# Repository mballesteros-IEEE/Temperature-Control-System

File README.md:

Temperature-Control-System
========================================

Automatic system to control temperature in a house. Project in development

Authors Manuel Ballesteros and Damián Junquera

Repository Contents
-------------------

* **/Firmware** - Example code 
* **/Hardware** - Eagle design files (.brd, .sch)
* **/Libraries** - Libraries for use with
* **/Software** - Related software
* **/Documentation** - Data sheets, additional product information

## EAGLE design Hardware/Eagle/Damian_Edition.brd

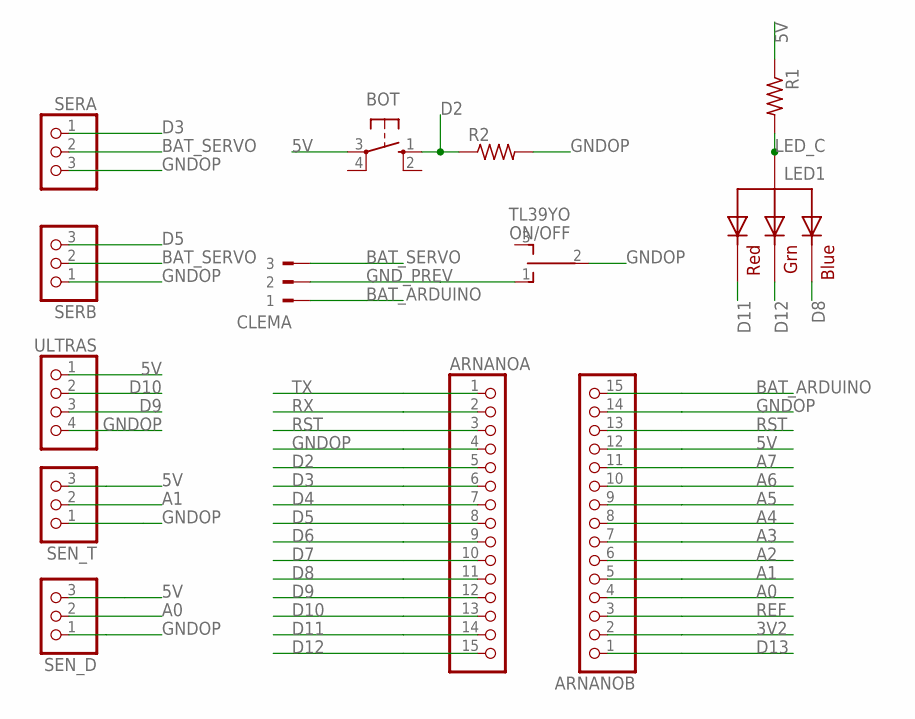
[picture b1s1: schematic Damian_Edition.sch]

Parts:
ARNANOA: PINHD-1X15; 1X15
ARNANOB: PINHD-1X15; 1X15
BOT: 10-XX; B3F-10XX
CLEMA: 90-3
LED1: RGBLED_CA-5MM; LED5MMRGB
ON/OFF: TL39YO; TL3XYO
R1, R2: R-US_0207/2V; 0207/2V
SEN_D: PINHD-1X3; 1X03
SEN_T: PINHD-1X3; 1X03
SERA: PINHD-1X3; 1X03
SERB: PINHD-1X3; 1X03
ULTRAS: PINHD-1X4; 1X04

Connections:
3V2: ARNANOB.2
5V: ARNANOB.12, BOT.3, R1.1, SEN_D.3, SEN_T.3, ULTRAS.1
A0: ARNANOB.4, SEN_D.2
A1: ARNANOB.5, SEN_T.2
A2: ARNANOB.6
A3: ARNANOB.7
A4: ARNANOB.8
A5: ARNANOB.9
A6: ARNANOB.10
A7: ARNANOB.11
BAT_ARDUINO: ARNANOB.15, CLEMA.1
BAT_SERVO: CLEMA.3, SERA.2, SERB.2
D2: ARNANOA.5, BOT.1 (S), R2.1
D3: ARNANOA.6, SERA.1
D4: ARNANOA.7
D5: ARNANOA.8, SERB.3
D6: ARNANOA.9
D7: ARNANOA.10
D8: ARNANOA.11, LED1.4 (BLUE)
D9: ARNANOA.12, ULTRAS.3
D10: ARNANOA.13, ULTRAS.2
D11: ARNANOA.14, LED1.1 (RED)
D12: ARNANOA.15, LED1.3 (GREEN)
D13: ARNANOB.1
GNDOP: ARNANOA.4, ARNANOB.14, ON/OFF.2, R2.2, SEN_D.1, SEN_T.1, SERA.3, SERB.1, ULTRAS.4
GND_PREV: CLEMA.2, ON/OFF.1 (O)
LED_C: LED1.2 (VCC), R1.2
REF: ARNANOB.3
RST: ARNANOA.3, ARNANOB.13
RX: ARNANOA.2
TX: ARNANOA.1

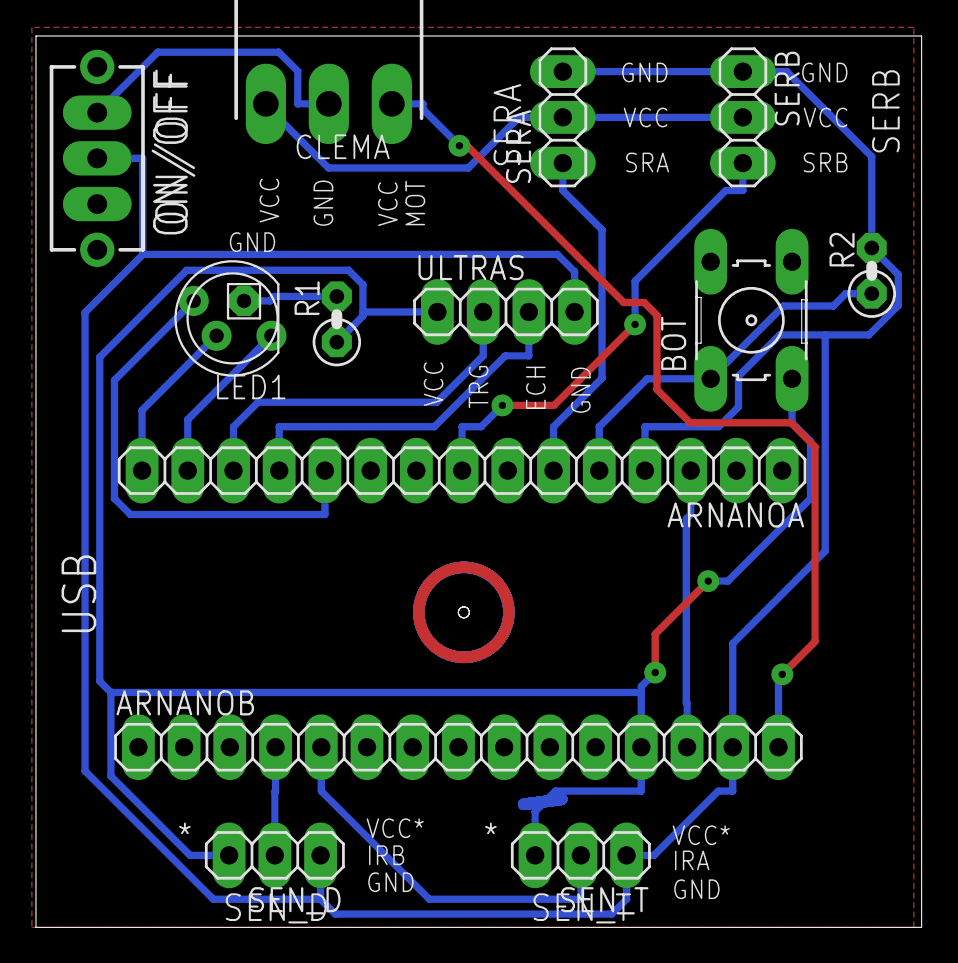
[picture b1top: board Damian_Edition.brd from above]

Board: 2 copper layers, 49.2 x 49.5 mm, 13 parts (0 on the bottom side), 17 nets.

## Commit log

2017-05-01 Update Readme and added .gitignore file
2017-05-01 Example of firmware tested with LCD 5110 and Arduino Nano. Added libraries for managing display Nokia LCD 5110.
2017-05-03 Added block diagram with all elements in automatic system
2017-05-11 Added first prototype of Hardware
2017-05-24 Create eagle folder
